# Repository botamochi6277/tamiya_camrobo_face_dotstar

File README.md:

# TAMIYA CAMROBO FACE DOTSTAR

An extension board for the face of [TAMIYA Cam-Program Robot](https://www.tamiya.com/english/products/70227/index.htm). 
This board has RGB LEDs and an audio amp.
This board is designed for Raspberry Pi.

- LED: SK9822, compatible chip of APA102. It is a RGB LED including a controller communicate with SPI. 
- Audio AMP: [AKIZUKI AMP Module](http://akizukidenshi.com/catalog/g/gK-08217/) using PAM8012. 
- Speaker: Small speaker you can buy from [AKIZUKI](http://akizukidenshi.com/catalog/g/gP-10128/). You need replace it because the speaker works in 3V (I failed to select.)

The board in v1.0 (photo version) have no wire between `IN-` and `GND`. I added wire for the connection. 

LICENCE: [Open Source Hardware](https://www.oshwa.org/definition/)

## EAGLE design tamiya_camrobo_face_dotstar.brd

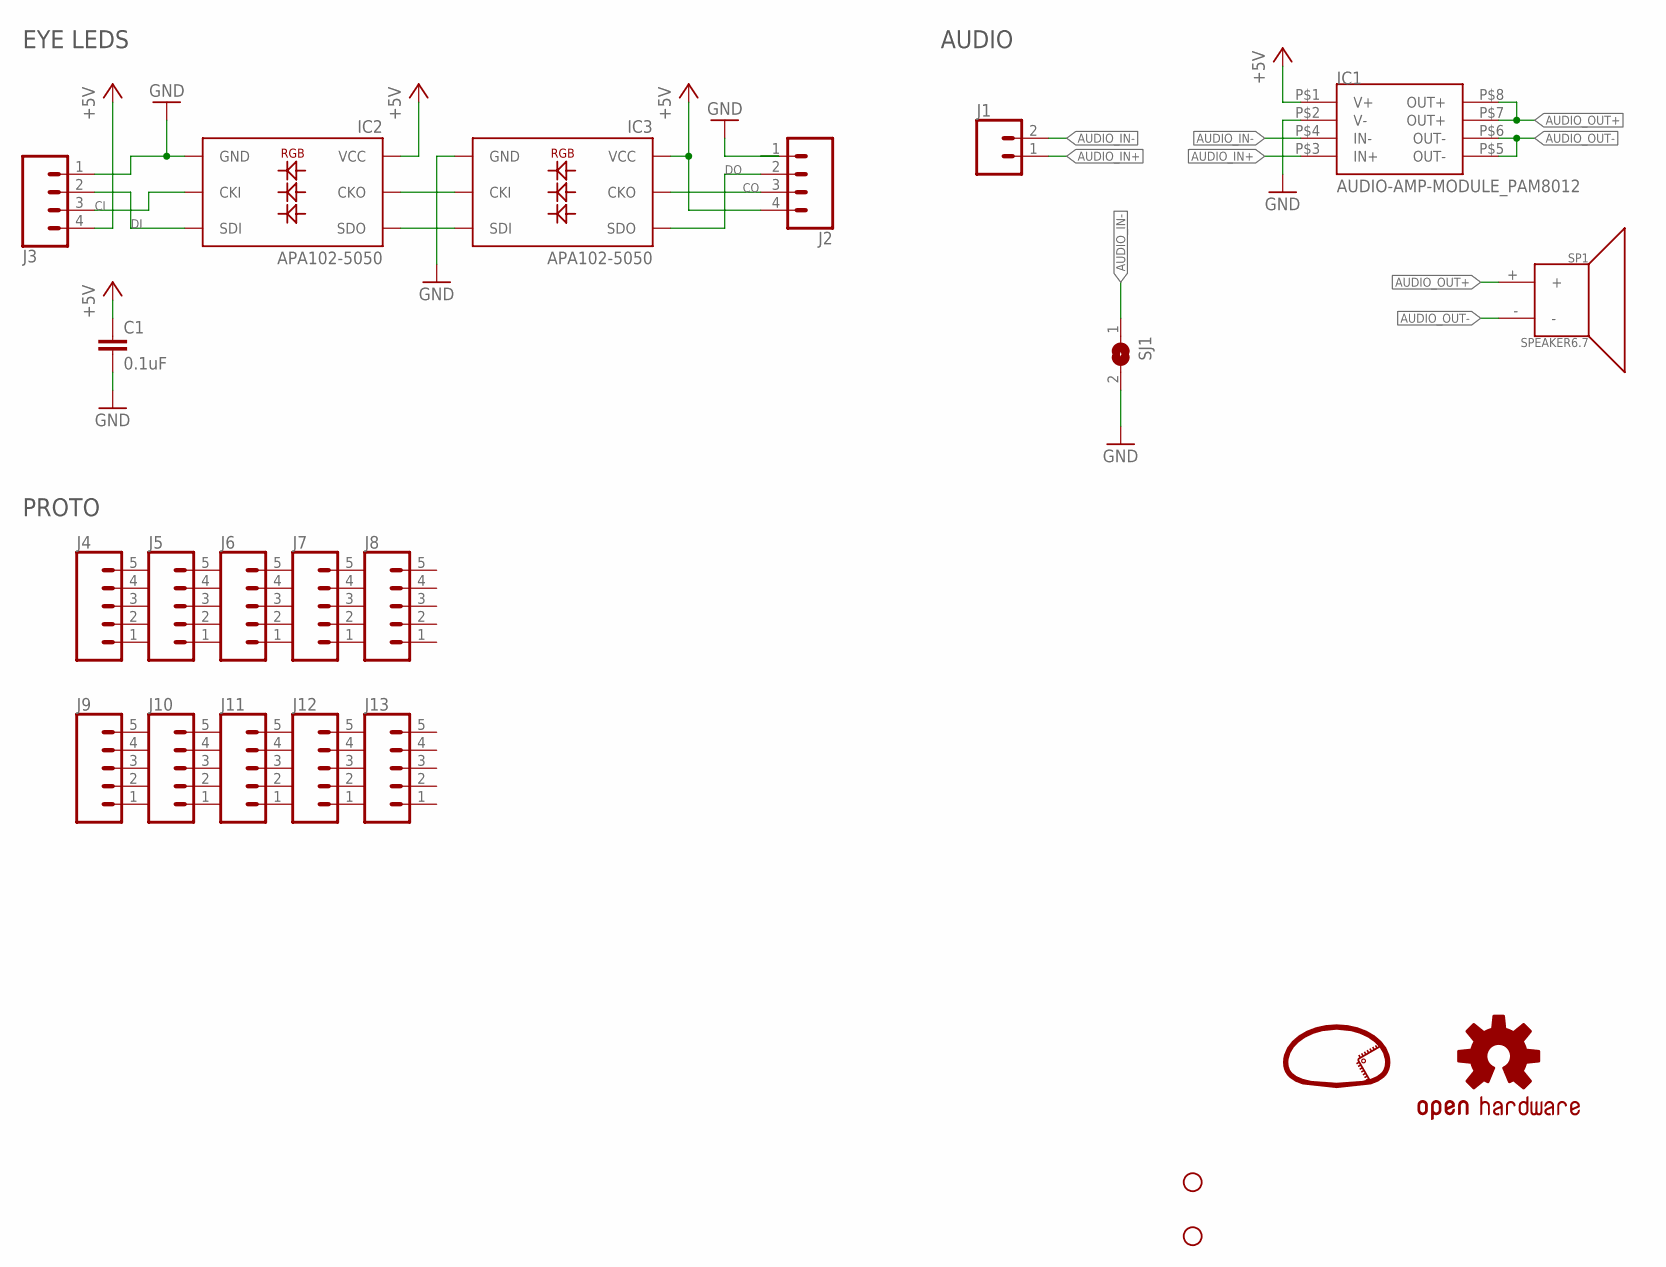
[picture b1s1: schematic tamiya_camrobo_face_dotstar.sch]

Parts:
C1: 0.1uF; C1608
H1, H2: STAND-OFF
IC1: AUDIO-AMP-MODULE_PAM8012; AE-PAM8012
IC2, IC3: APA102-5050; APA102C-5050
J1: CONN_02; 1X02
J2, J3: CONN_04; 1X04
J4, J5, J6, J7, J8, J9, J10, J11, J12, J13: CONN_05NO_SILK; 1X05_NO_SILK
LOGO1: LOGO
LOGO2: OSHW-LOGOS; OSHW-LOGO-S
SJ1: SJ
SP1: SPEAKER6.7; SPEAKER-6.7MM

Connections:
+5V: C1.1, IC1.P$1 (V+), IC2.VCC, IC3.VCC, J2.4, J3.4
AUDIO_IN+: IC1.P$3 (IN+), J1.1
AUDIO_IN-: IC1.P$4 (IN-), J1.2, SJ1.1
AUDIO_OUT+: IC1.P$7 (OUT+), IC1.P$8 (OUT+), SP1.+
AUDIO_OUT-: IC1.P$5 (OUT-), IC1.P$6 (OUT-), SP1.-
CI: IC2.CKI, J3.3
CO: IC3.CKO, J2.3
DI: IC2.SDI, J3.2
DO: IC3.SDO, J2.2
GND: C1.2, IC1.P$2 (V-), IC2.GND, IC3.GND, J2.1, J3.1, SJ1.2
unnamed: IC2.SDO, IC3.SDI
unnamed: IC2.CKO, IC3.CKI

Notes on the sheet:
EYE LEDS
AUDIO
PROTO

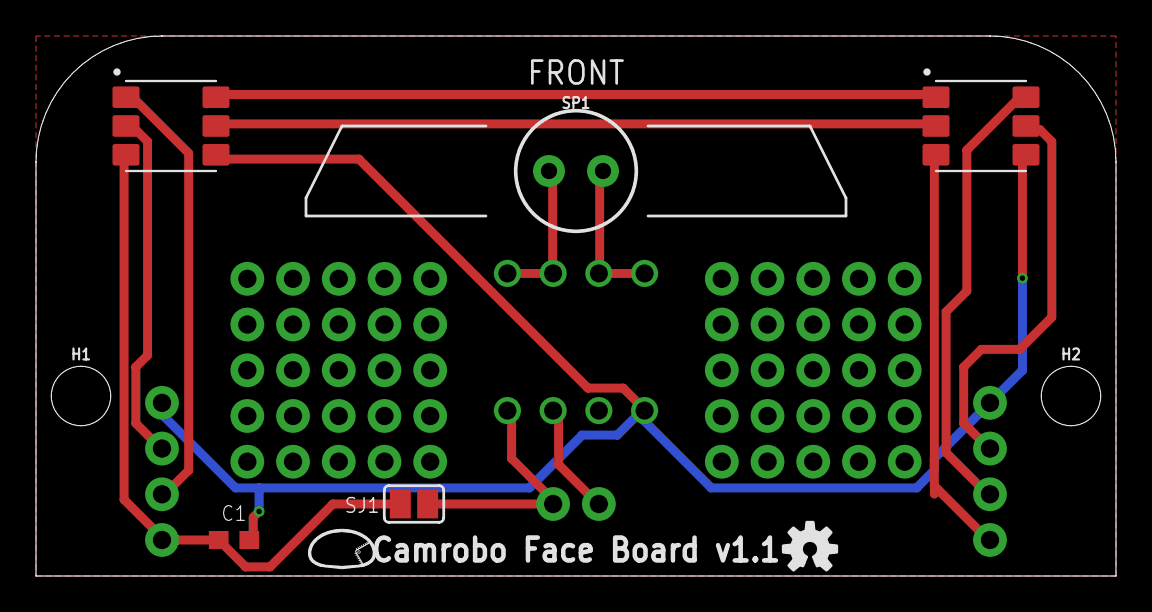
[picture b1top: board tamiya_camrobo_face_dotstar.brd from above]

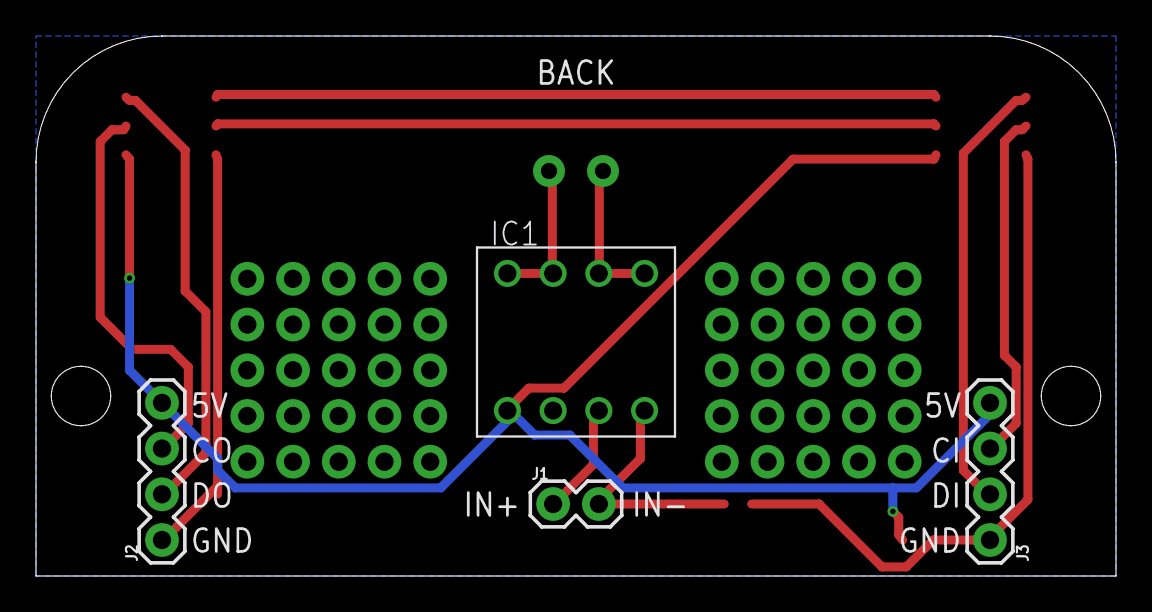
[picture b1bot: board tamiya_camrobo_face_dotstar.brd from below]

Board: 2 copper layers, 60.0 x 30.0 mm, 23 parts (4 on the bottom side), 12 nets.

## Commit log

2020-08-09 add licence discription

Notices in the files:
parts and their libraries:
SparkFun-Hardware: Licensing: Creative Commons ShareAlike 4.0 International - https://creativecommons.org/licenses/by-sa/4.0
